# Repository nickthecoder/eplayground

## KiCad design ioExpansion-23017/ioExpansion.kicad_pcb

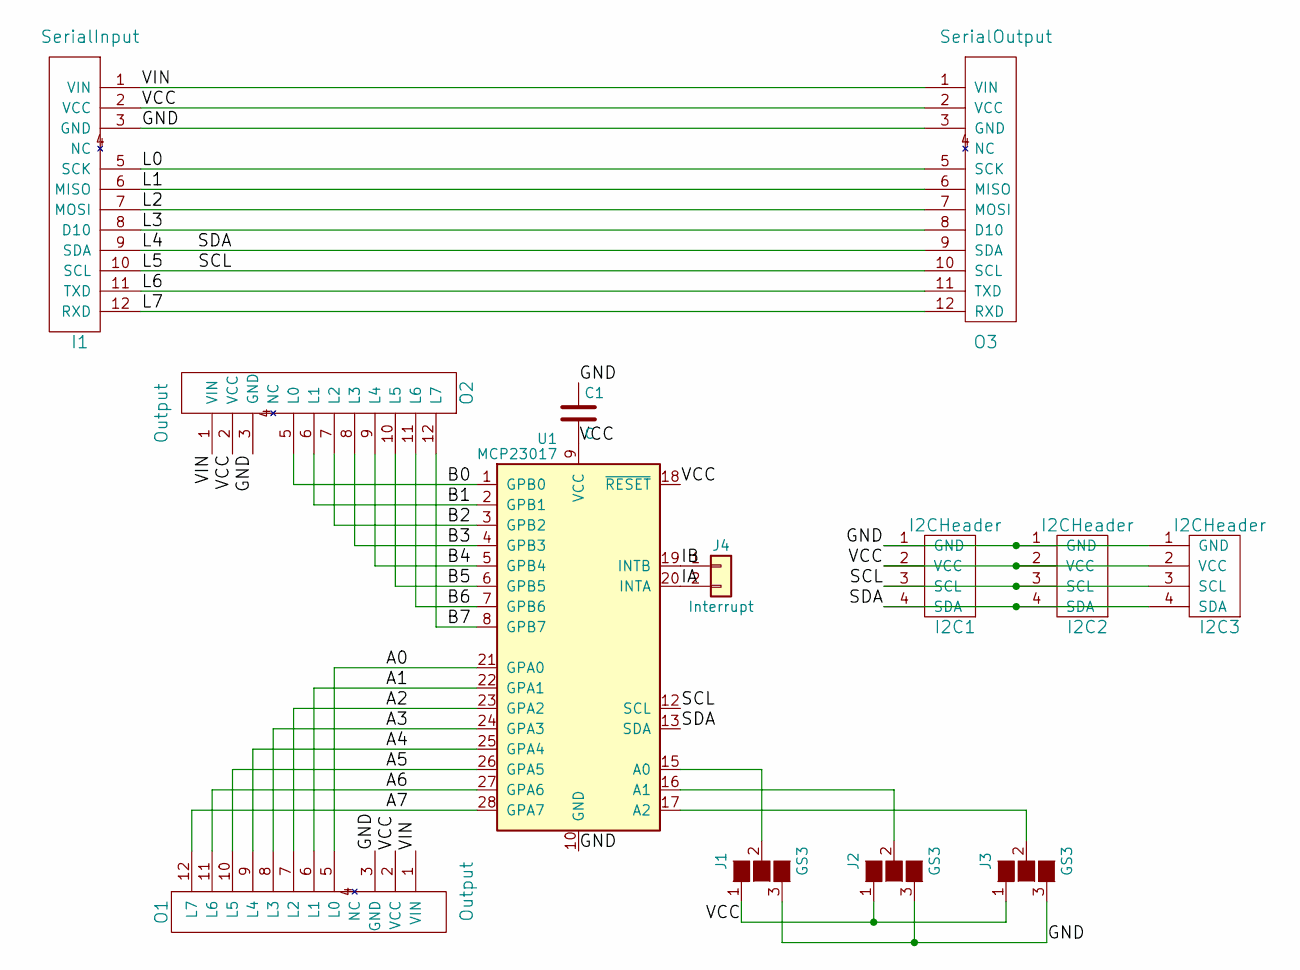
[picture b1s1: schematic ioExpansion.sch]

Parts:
C1: C; C_Disc_D3.8mm_W2.6mm_P2.50mm
I1: SerialInput; Socket_Strip_Straight_1x12_Pitch2.54mm
I2C1, I2C2, I2C3: I2CHeader; Pin_Header_Straight_1x04_Pitch2.54mm
J1, J2, J3: GS3
J4: Interrupt; Pin_Header_Straight_1x02_Pitch2.54mm
O1, O2: Output; Socket_Strip_Straight_1x12_Pitch2.54mm
O3: SerialOutput; Socket_Strip_Straight_1x12_Pitch2.54mm
U1: MCP23017; DIP-28_W7.62mm

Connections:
/A0: O1.5 (L0), U1.21 (GPA0)
/A1: O1.6 (L1), U1.22 (GPA1)
/A2: O1.7 (L2), U1.23 (GPA2)
/A3: O1.8 (L3), U1.24 (GPA3)
/A4: O1.9 (L4), U1.25 (GPA4)
/A5: O1.10 (L5), U1.26 (GPA5)
/A6: O1.11 (L6), U1.27 (GPA6)
/A7: O1.12 (L7), U1.28 (GPA7)
/B0: O2.5 (L0), U1.1 (GPB0)
/B1: O2.6 (L1), U1.2 (GPB1)
/B2: O2.7 (L2), U1.3 (GPB2)
/B3: O2.8 (L3), U1.4 (GPB3)
/B4: O2.9 (L4), U1.5 (GPB4)
/B5: O2.10 (L5), U1.6 (GPB5)
/B6: O2.11 (L6), U1.7 (GPB6)
/B7: O2.12 (L7), U1.8 (GPB7)
/GND: C1.1, I1.3 (GND), I2C1.1 (GND), I2C2.1 (GND), I2C3.1 (GND), J1.3 (G3), J2.3 (G3), J3.3 (G3), O1.3 (GND), O2.3 (GND), O3.3 (GND), U1.10 (GND)
/IA: J4.2, U1.20 (INTA)
/IB: J4.1, U1.19 (INTB)
/L0: I1.5 (SCK), O3.5 (SCK); also elsewhere on the board
/L1: I1.6 (MISO), O3.6 (MISO); also elsewhere on the board
/L2: I1.7 (MOSI), O3.7 (MOSI); also elsewhere on the board
/L3: I1.8 (D10), O3.8 (D10); also elsewhere on the board
/L4: I1.9 (SDA), I2C1.4 (SDA), I2C2.4 (SDA), I2C3.4 (SDA), O3.9 (SDA), U1.13 (SDA); also elsewhere on the board
/L5: I1.10 (SCL), I2C1.3 (SCL), I2C2.3 (SCL), I2C3.3 (SCL), O3.10 (SCL), U1.12 (SCL); also elsewhere on the board
/L6: I1.11 (TXD), O3.11 (TXD); also elsewhere on the board
/L7: I1.12 (RXD), O3.12 (RXD); also elsewhere on the board
/VCC: C1.2, I1.2 (VCC), I2C1.2 (VCC), I2C2.2 (VCC), I2C3.2 (VCC), J1.1 (G1), J2.1 (G1), J3.1 (G1), O1.2 (VCC), O2.2 (VCC), O3.2 (VCC), U1.9 (VCC), U1.18 (~RESET)
/VIN: I1.1 (VIN), O1.1 (VIN), O2.1 (VIN), O3.1 (VIN)
unnamed: J1.2 (G2), U1.15 (A0)
unnamed: J2.2 (G2), U1.16 (A1)
unnamed: J3.2 (G2), U1.17 (A2)

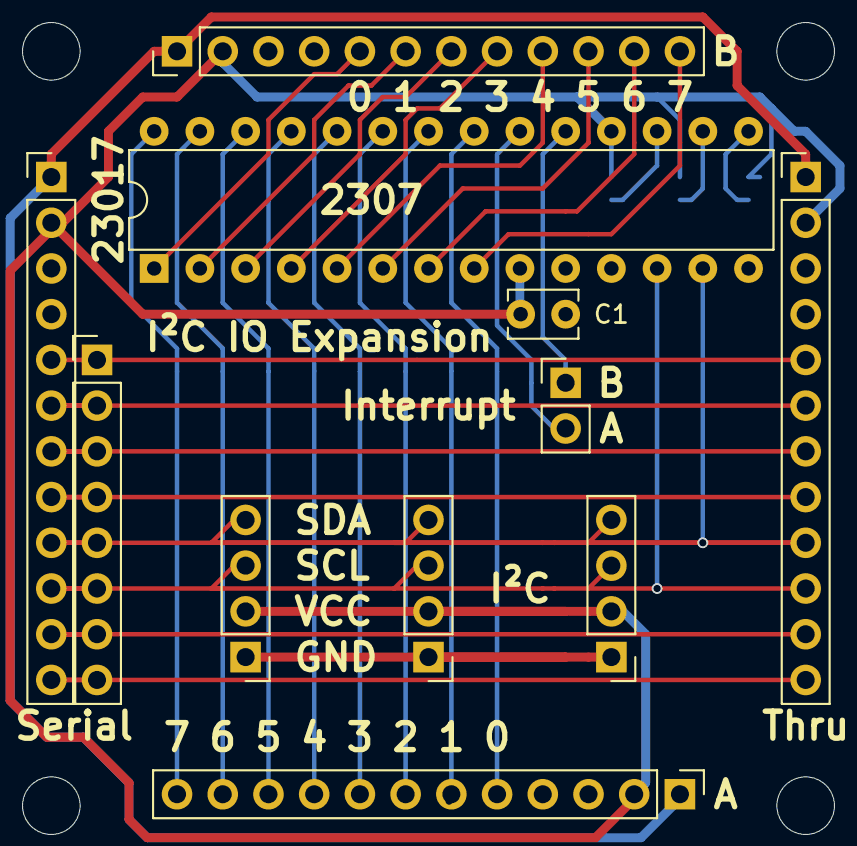
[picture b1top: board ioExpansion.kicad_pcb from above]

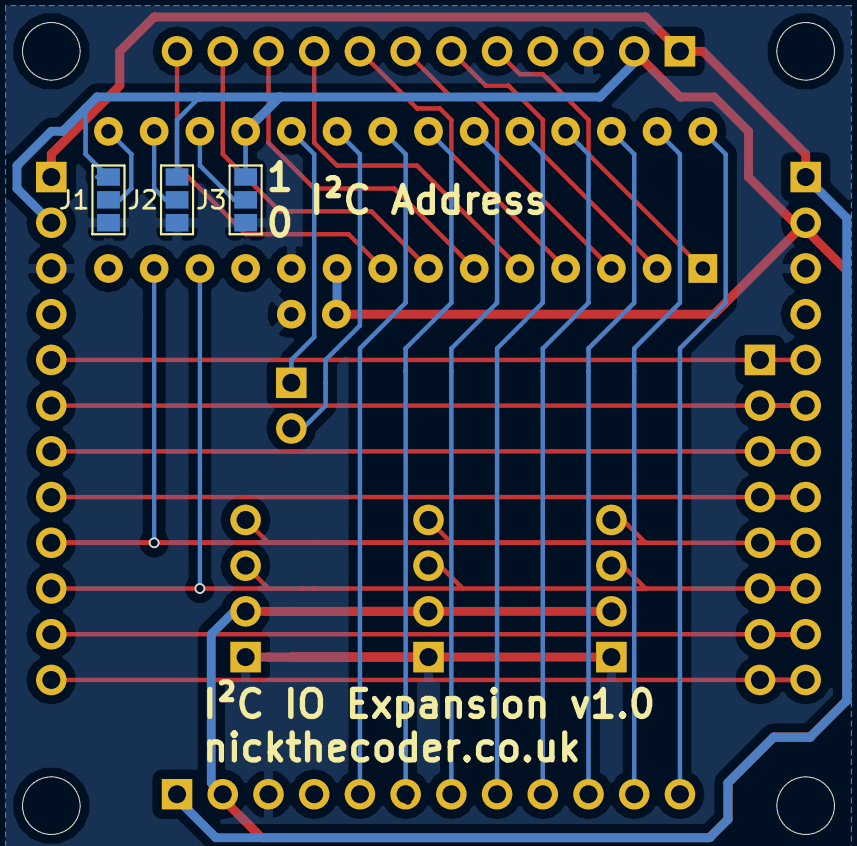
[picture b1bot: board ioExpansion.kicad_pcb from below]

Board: 2 copper layers, 16 parts (3 on the bottom side), 32 nets.

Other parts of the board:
H1: Headers8; Pin_Header_Straight_1x08_Pitch2.54mm
M3, M3#2: MountingHole_3.2mm_M3

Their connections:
/L0: H1.1; also elsewhere on the board
/L1: H1.2; also elsewhere on the board
/L2: H1.3; also elsewhere on the board
/L3: H1.4; also elsewhere on the board
/L4: H1.5; also elsewhere on the board
/L5: H1.6; also elsewhere on the board
/L6: H1.7; also elsewhere on the board
/L7: H1.8; also elsewhere on the board

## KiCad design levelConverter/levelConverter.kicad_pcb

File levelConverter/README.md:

Level Converter
===============

A bi-directional level converter. Place this between a 5V microcontroller, and 3.3V modules.
Uses a voltage regulator to convert the 5V from the microcontroller to 3.3, and mosfets to convert
all eight signals.

## Notes

I think I should have added headers to enable/disable each of the eight lines as it is likely that a project
will need to only convert SOME of the GPIOs. On second thoughts, it should be fine. Need to check!

There is a half-sized version of this module, which uses 9 pin resistor packs, instead of the axial resistors
on this module.

## Version History

### Version 1.0

At the time of writing, I haven't printed (or tested) this module, because I favour the half-sized version.

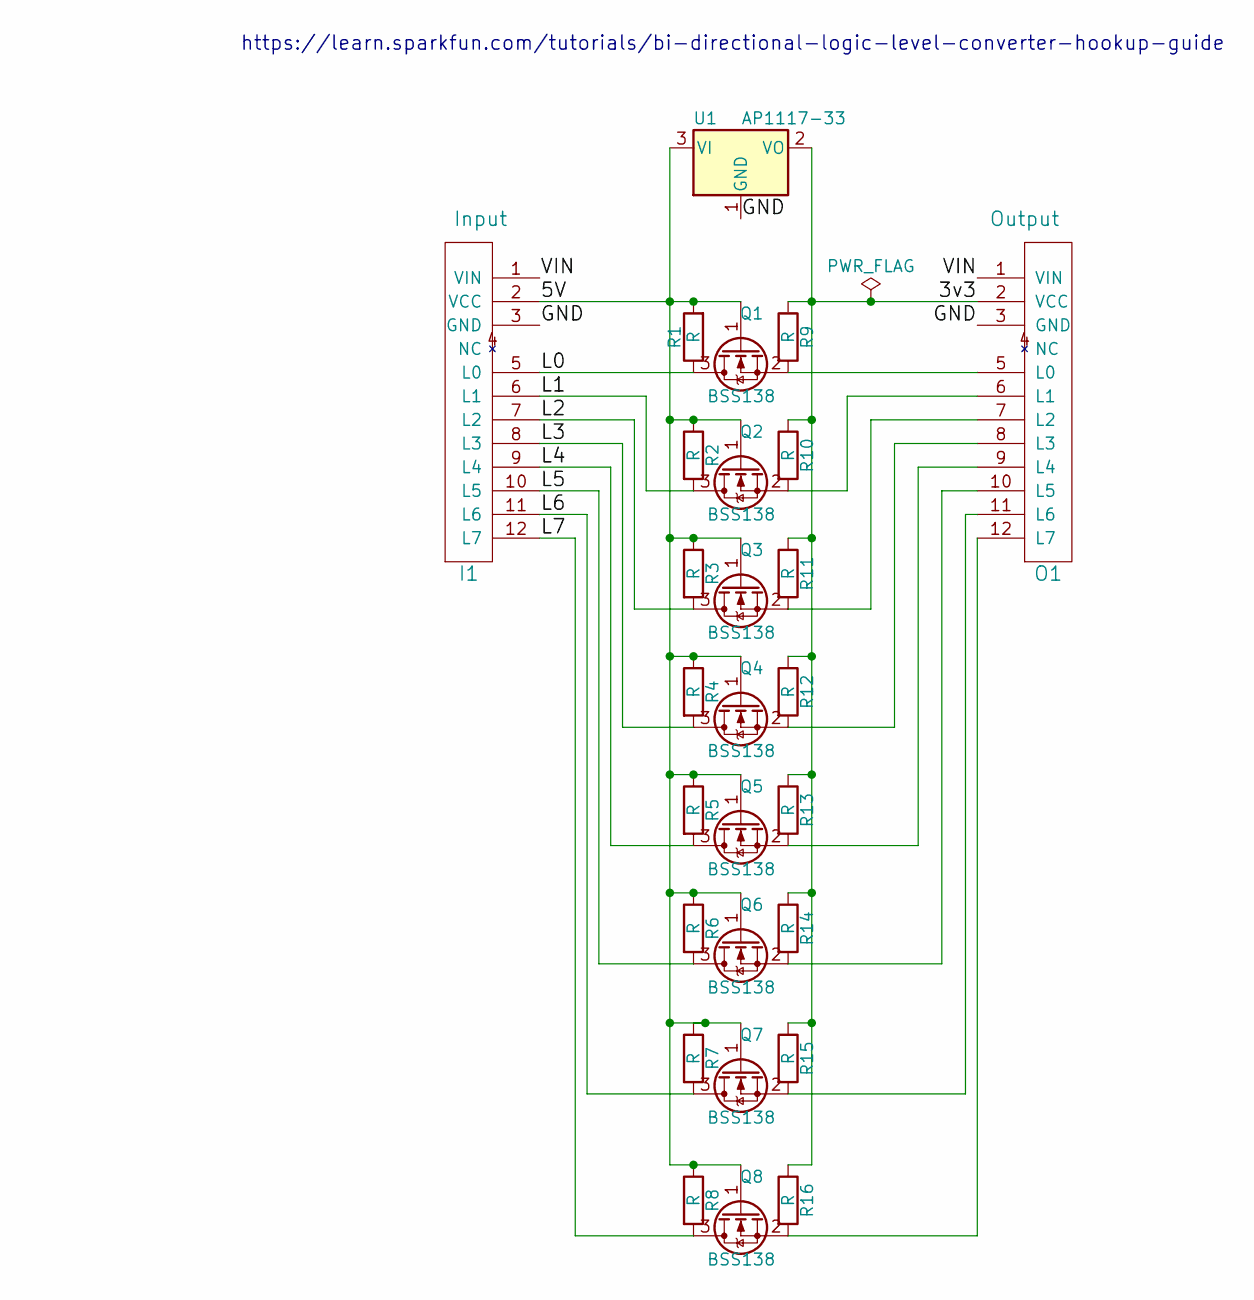
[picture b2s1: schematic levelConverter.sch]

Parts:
I1: Input; Pin_Header_Straight_1x12_Pitch2.54mm
O1: Output; Socket_Strip_Straight_1x12_Pitch2.54mm
Q1, Q2, Q3, Q4, Q5, Q6, Q7, Q8: BSS138; SOT-23
R1, R2, R3, R4, R5, R6, R7, R8, R9, R10, R11, R12, R13, R14, R15, R16: R; R_Axial_DIN0204_L3.6mm_D1.6mm_P7.62mm_Horizontal
U1: AP1117-33; SOT-223-3Lead_TabPin2

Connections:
/3v3: O1.2 (VCC), R9.1, R10.1, R11.1, R12.1, R13.1, R14.1, R15.1, R16.1, U1.2 (VO)
/5V: I1.2 (VCC), Q1.1 (G), Q2.1 (G), Q3.1 (G), Q4.1 (G), Q5.1 (G), Q6.1 (G), Q7.1 (G), Q8.1 (G), R1.2, R2.1, R3.1, R4.1, R5.1, R6.1, R7.1, R8.1, U1.3 (VI)
/GND: I1.3 (GND), O1.3 (GND), U1.1 (GND)
/L0: I1.5 (L0), Q1.3 (D), R1.1
/L1: I1.6 (L1), Q2.3 (D), R2.2
/L2: I1.7 (L2), Q3.3 (D), R3.2
/L3: I1.8 (L3), Q4.3 (D), R4.2
/L4: I1.9 (L4), Q5.3 (D), R5.2
/L5: I1.10 (L5), Q6.3 (D), R6.2
/L6: I1.11 (L6), Q7.3 (D), R7.2
/L7: I1.12 (L7), Q8.3 (D), R8.2
/VIN: I1.1 (VIN), O1.1 (VIN)
unnamed: O1.5 (L0), Q1.2 (S), R9.2
unnamed: O1.6 (L1), Q2.2 (S), R10.2
unnamed: O1.7 (L2), Q3.2 (S), R11.2
unnamed: O1.8 (L3), Q4.2 (S), R12.2
unnamed: O1.9 (L4), Q5.2 (S), R13.2
unnamed: O1.10 (L5), Q6.2 (S), R14.2
unnamed: O1.11 (L6), Q7.2 (S), R15.2
unnamed: O1.12 (L7), Q8.2 (S), R16.2

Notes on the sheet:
https://learn.sparkfun.com/tutorials/bi-directional-logic-level-converter-hookup-guide

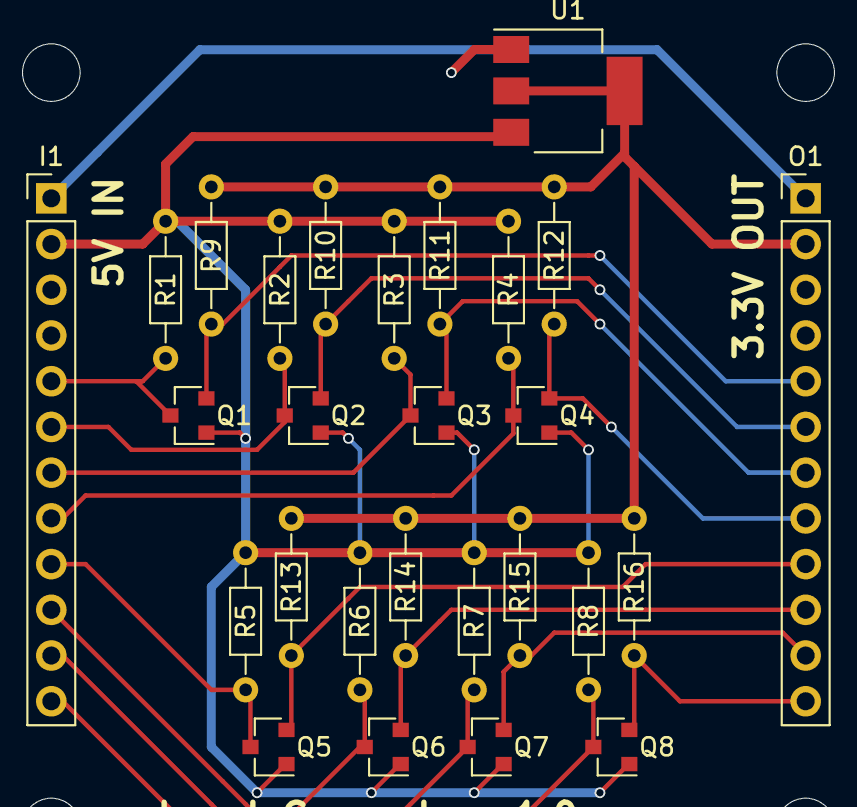
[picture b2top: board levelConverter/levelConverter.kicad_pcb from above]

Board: 2 copper layers, 29 parts (0 on the bottom side), 20 nets.

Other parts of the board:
M3, M3#2: MountingHole_3.2mm_M3

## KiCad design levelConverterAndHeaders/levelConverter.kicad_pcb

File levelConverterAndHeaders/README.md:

Level Converter
===============

A bi-directional level converter. Place this between a 5V microcontroller, and 3.3V modules.
Uses a voltage regulator to convert the 5V from the microcontroller to 3.3, and mosfets to convert
all eight signals.

This is a half-sized module. There is also a full sized module, which uses regular axial resistors, instead of the
9 pin resistor networks used by this module. The choice is yours!

Headers
=======

Another half-sized module, which exposes each data pin in a triple header, with VCC and GND.
This is particularly useful for servos.

## Version History

### Version 1.0

At the time of writing I haven't tested these modules.

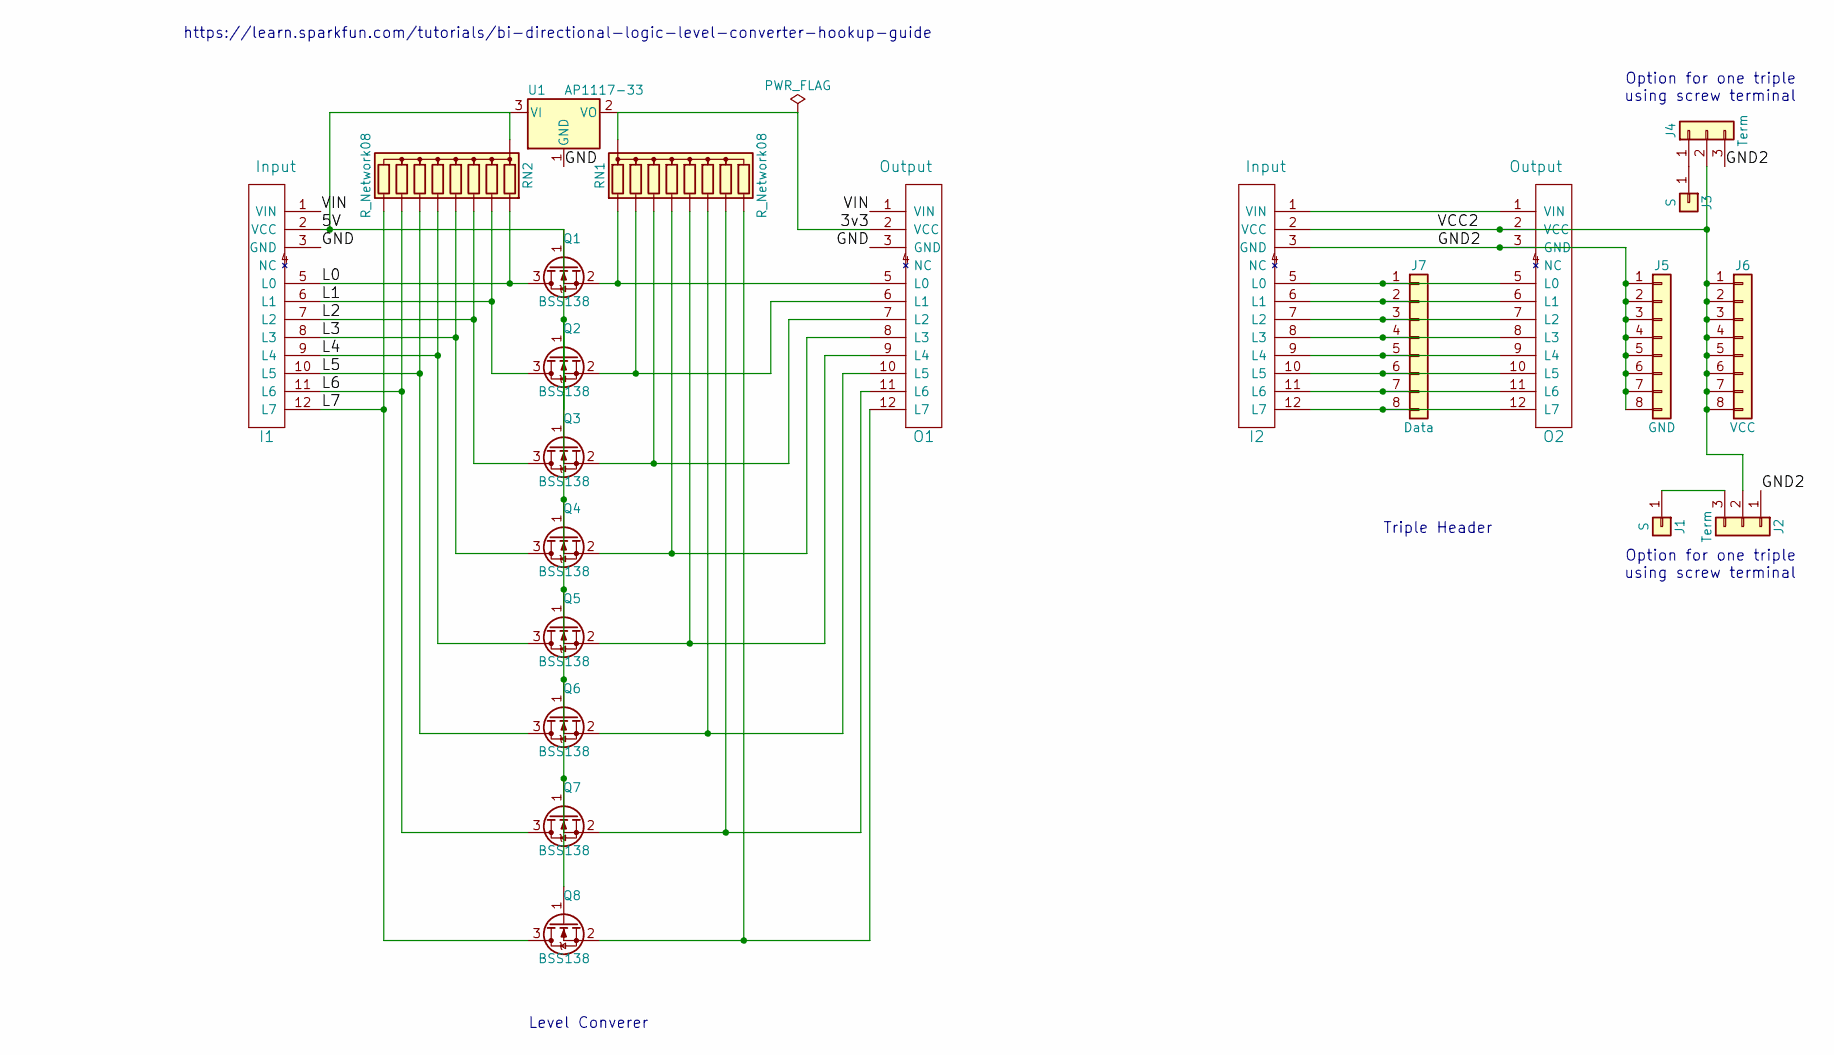
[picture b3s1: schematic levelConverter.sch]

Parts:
I1, I2: Input; Pin_Header_Straight_1x12_Pitch2.54mm
J1, J3: S; Pin_Header_Straight_1x01_Pitch2.54mm
J2, J4: Term; TerminalBlock_Pheonix_MPT-2.54mm_3pol
J5: GND; Pin_Header_Straight_1x08_Pitch2.54mm
J6: VCC; Pin_Header_Straight_1x08_Pitch2.54mm
J7: Data; Pin_Header_Straight_1x08_Pitch2.54mm
O1, O2: Output; Socket_Strip_Straight_1x12_Pitch2.54mm
Q1, Q2, Q3, Q4, Q5, Q6, Q7, Q8: BSS138; SOT-23
RN1, RN2: R_Network08; R_Array_SIP9
U1: AP1117-33; SOT-223-3Lead_TabPin2

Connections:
/3v3: O1.2 (VCC), RN1.1 (common), U1.2 (VO)
/5V: I1.2 (VCC), Q1.1 (G), Q2.1 (G), Q3.1 (G), Q4.1 (G), Q5.1 (G), Q6.1 (G), Q7.1 (G), Q8.1 (G), RN2.1 (common), U1.3 (VI)
/GND: I1.3 (GND), O1.3 (GND), U1.1 (GND)
/GND2: I2.3 (GND), J2.1, J4.3, J5.1, J5.2, J5.3, J5.4, J5.5, J5.6, J5.7, J5.8, O2.3 (GND)
/L0: I1.5 (L0), Q1.3 (D), RN2.2 (R1)
/L1: I1.6 (L1), Q2.3 (D), RN2.3 (R2)
/L2: I1.7 (L2), Q3.3 (D), RN2.4 (R3)
/L3: I1.8 (L3), Q4.3 (D), RN2.5 (R4)
/L4: I1.9 (L4), Q5.3 (D), RN2.6 (R5)
/L5: I1.10 (L5), Q6.3 (D), RN2.7 (R6)
/L6: I1.11 (L6), Q7.3 (D), RN2.8 (R7)
/L7: I1.12 (L7), Q8.3 (D), RN2.9 (R8)
/VCC2: I2.2 (VCC), J2.2, J4.2, J6.1, J6.2, J6.3, J6.4, J6.5, J6.6, J6.7, J6.8, O2.2 (VCC)
/VIN: I1.1 (VIN), O1.1 (VIN)
unnamed: I2.1 (VIN), O2.1 (VIN)
unnamed: I2.5 (L0), J7.1, O2.5 (L0)
unnamed: I2.6 (L1), J7.2, O2.6 (L1)
unnamed: I2.7 (L2), J7.3, O2.7 (L2)
unnamed: I2.8 (L3), J7.4, O2.8 (L3)
unnamed: I2.9 (L4), J7.5, O2.9 (L4)
unnamed: I2.10 (L5), J7.6, O2.10 (L5)
unnamed: I2.11 (L6), J7.7, O2.11 (L6)
unnamed: I2.12 (L7), J7.8, O2.12 (L7)
unnamed: J1.1, J2.3
unnamed: J3.1, J4.1
unnamed: O1.5 (L0), Q1.2 (S), RN1.2 (R1)
unnamed: O1.6 (L1), Q2.2 (S), RN1.3 (R2)
unnamed: O1.7 (L2), Q3.2 (S), RN1.4 (R3)
unnamed: O1.8 (L3), Q4.2 (S), RN1.5 (R4)
unnamed: O1.9 (L4), Q5.2 (S), RN1.6 (R5)
unnamed: O1.10 (L5), Q6.2 (S), RN1.7 (R6)
unnamed: O1.11 (L6), Q7.2 (S), RN1.8 (R7)
unnamed: O1.12 (L7), Q8.2 (S), RN1.9 (R8)

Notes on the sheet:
https://learn.sparkfun.com/tutorials/bi-directional-logic-level-converter-hookup-guide
Level Converer
Triple Header
Option for one triple using screw terminal

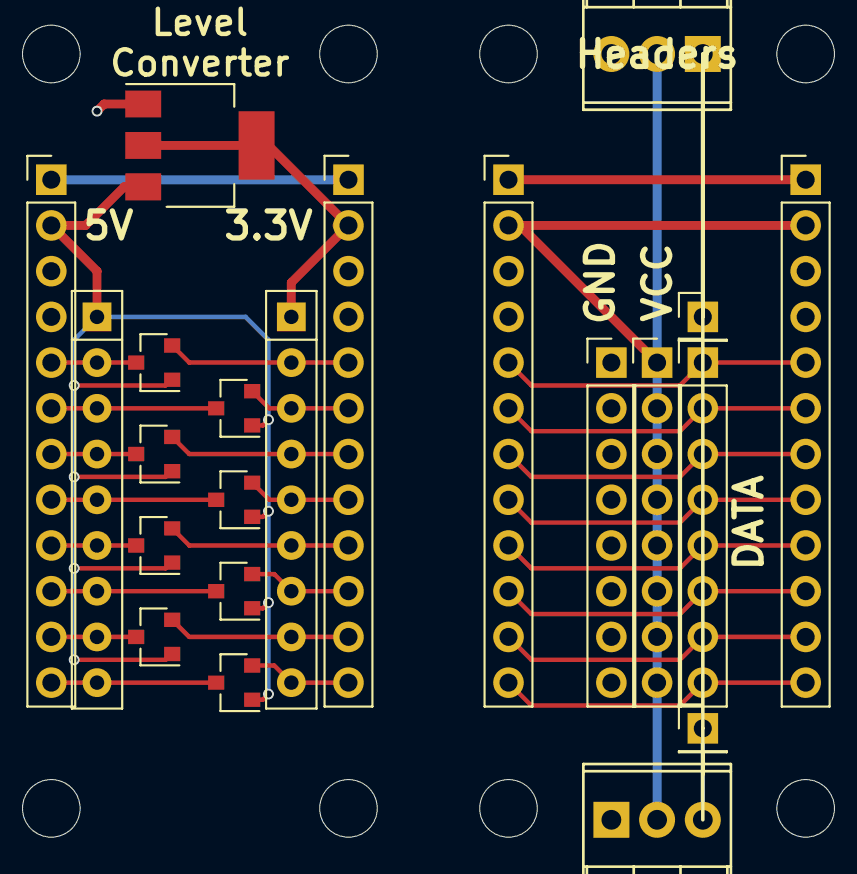
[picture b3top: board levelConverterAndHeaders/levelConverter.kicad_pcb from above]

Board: 2 copper layers, 26 parts (0 on the bottom side), 33 nets.

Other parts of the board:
M3, M3#2, M3#3, M3#4: MountingHole_3.2mm_M3

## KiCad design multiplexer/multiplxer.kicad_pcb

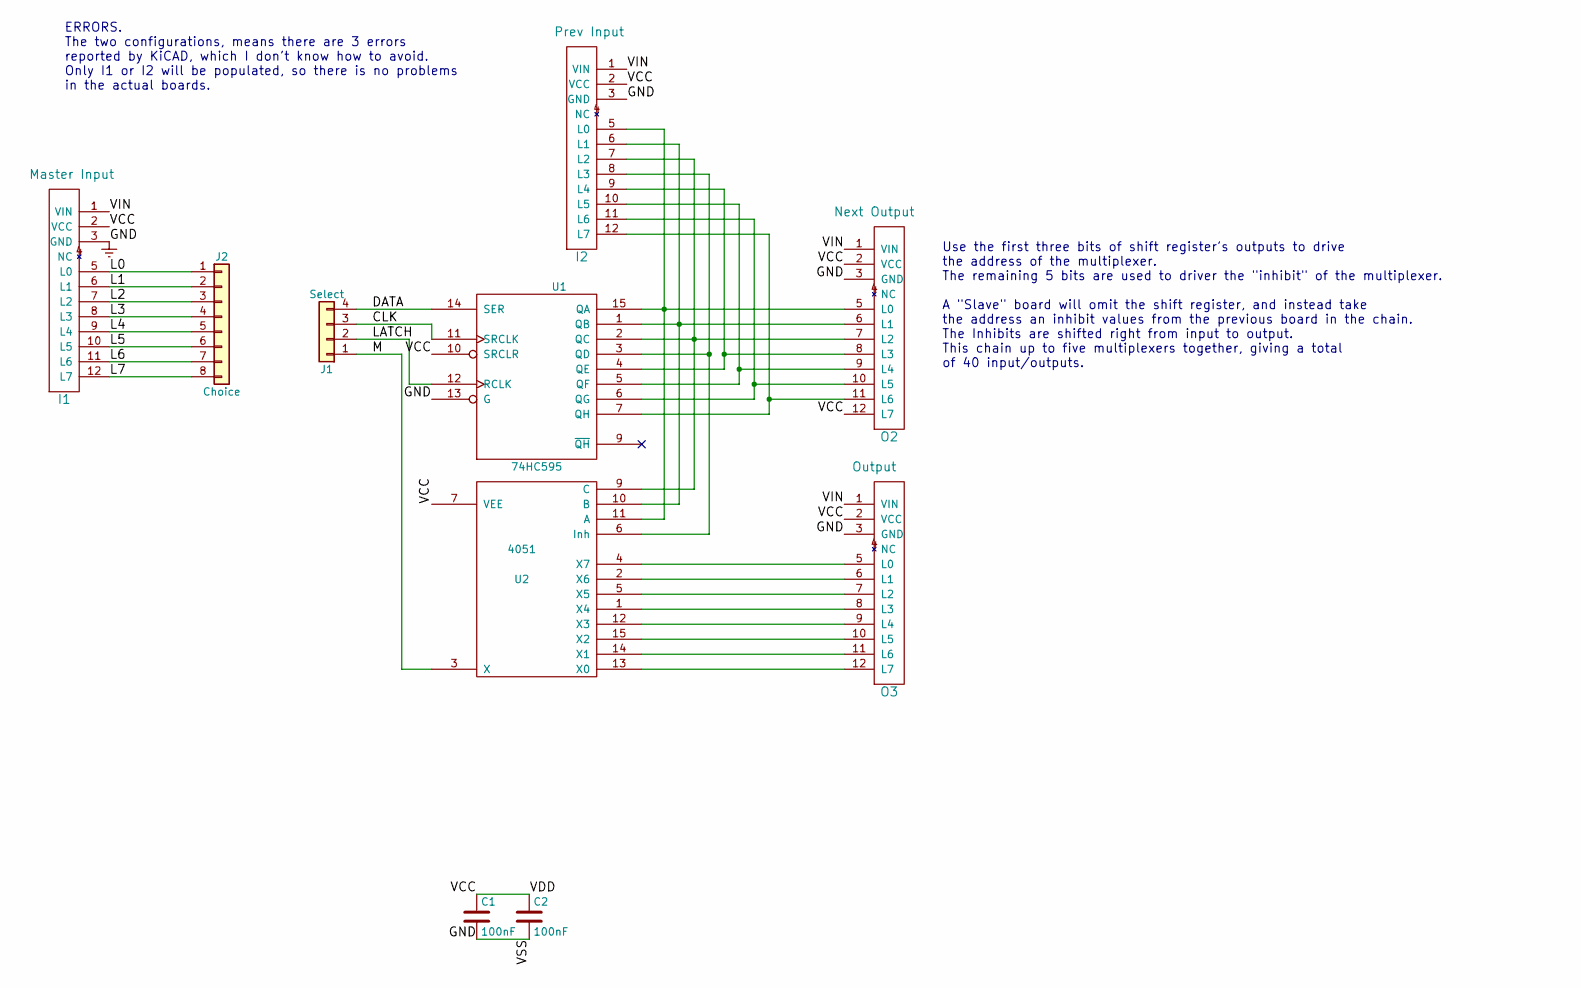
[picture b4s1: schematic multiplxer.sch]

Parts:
C1, C2: 100nF; C_Disc_D3.8mm_W2.6mm_P2.50mm
I1: Master Input; Pin_Header_Straight_1x12_Pitch2.54mm
I2: Prev Input; Pin_Header_Straight_1x12_Pitch2.54mm
J1: Select; Pin_Header_Straight_1x04_Pitch2.54mm
J2: Choice; Pin_Header_Straight_1x08_Pitch2.54mm
O2: Next Output; Socket_Strip_Straight_1x12_Pitch2.54mm
O3: Output; Socket_Strip_Straight_1x12_Pitch2.54mm
U1: 74HC595; DIP-16_W7.62mm
U2: 4051; DIP-16_W7.62mm

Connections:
/CLK: J1.3, U1.11 (SRCLK)
/DATA: J1.4, U1.14 (SER)
/L0: I1.5 (L0), J2.1
/L1: I1.6 (L1), J2.2
/L2: I1.7 (L2), J2.3
/L3: I1.8 (L3), J2.4
/L4: I1.9 (L4), J2.5
/L5: I1.10 (L5), J2.6
/L6: I1.11 (L6), J2.7
/L7: I1.12 (L7), J2.8
/LATCH: J1.2, U1.12 (RCLK)
/M: J1.1, U2.3 (X)
/VIN: I1.1 (VIN), I2.1 (VIN), O2.1 (VIN), O3.1 (VIN)
Earth: C1.2, C2.2, I1.3 (GND), I2.3 (GND), O2.3 (GND), O3.3 (GND), U1.8 (GND), U1.13 (G), U2.8 (VSS)
unnamed: I2.5 (L0), O2.5 (L0), U1.15 (QA), U2.11 (A)
unnamed: I2.6 (L1), O2.6 (L1), U1.1 (QB), U2.10 (B)
unnamed: I2.7 (L2), O2.7 (L2), U1.2 (QC), U2.9 (C)
unnamed: I2.8 (L3), U1.3 (QD), U2.6 (Inh)
unnamed: I2.9 (L4), O2.8 (L3), U1.4 (QE)
unnamed: I2.10 (L5), O2.9 (L4), U1.5 (QF)
unnamed: I2.11 (L6), O2.10 (L5), U1.6 (QG)
unnamed: I2.12 (L7), O2.11 (L6), U1.7 (QH)
unnamed: O3.5 (L0), U2.4 (X7)
unnamed: O3.6 (L1), U2.2 (X6)
unnamed: O3.7 (L2), U2.5 (X5)
unnamed: O3.8 (L3), U2.1 (X4)
unnamed: O3.9 (L4), U2.12 (X3)
unnamed: O3.10 (L5), U2.15 (X2)
unnamed: O3.11 (L6), U2.14 (X1)
unnamed: O3.12 (L7), U2.13 (X0)
VCC: C1.1, C2.1, I1.2 (VCC), I2.2 (VCC), O2.2 (VCC), O2.12 (L7), O3.2 (VCC), U1.10 (SRCLR), U1.16 (VCC), U2.7 (VEE), U2.16 (VDD)

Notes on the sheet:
Use the first three bits of shift register's outputs to drive the address of the multiplexer. The remaining 5 bits are used to driver the "inhibit" of the multiplexer. A "Slave" board will omit the shift register, and instead take the address an inhibit values from the previous board in the chain. 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
ERRORS. The two configurations, means there are 3 errors reported by KiCAD, which I don't know how to avoid. Only I1 or I2 will be populated, so there is no problems in the actual boards.

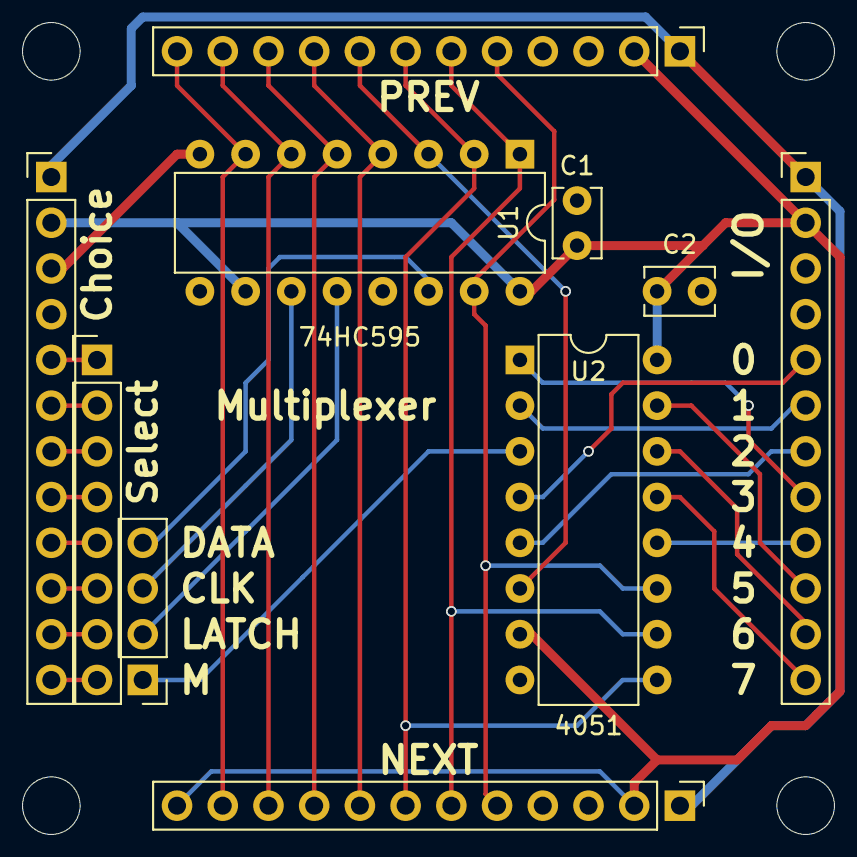
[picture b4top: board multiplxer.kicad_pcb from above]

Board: 2 copper layers, 12 parts (0 on the bottom side), 31 nets.

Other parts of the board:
M3, M3#2: MountingHole_3.2mm_M3

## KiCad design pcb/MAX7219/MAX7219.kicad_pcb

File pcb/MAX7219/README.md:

MAX 7219
========

The MAX 7219 can drive six eight segment displays, or a 6x8 LED matrix, as well as upto 16 buttons.

The module only has 8 buttons, however, you can switch between the two banks of buttons using a switch.

The outputs for the leds are exposed as simple header pins.

## Version History

### Version 1.0

At the time of writing, I haven't tested this module.

The name of the module is missing. It reads "Module Name". Oops.

### Version 1.1

Not printed.

Corrected the module name.

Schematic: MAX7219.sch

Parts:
C1, C2: 100pF; C_Disc_D3.0mm_W1.6mm_P2.50mm
H1: Headers8L; Pin_Header_Straight_1x08_Pitch2.54mm
I1: SerialInput; Pin_Header_Straight_1x12_Pitch2.54mm
J1: Conn_01x02; Pin_Header_Straight_1x02_Pitch2.54mm
J2: Conn_01x08; Pin_Header_Straight_1x08_Pitch2.54mm
J3: Conn_01x06; Pin_Header_Straight_1x06_Pitch2.54mm
O1: Output; Socket_Strip_Straight_1x12_Pitch2.54mm
SW1, SW2, SW3, SW4, SW5, SW6, SW7, SW8: SW_SPST; SW_SPST_EVQP0
SW9: SW_SPDT; SW_CuK_JS202011CQN_DPDT_Straight
U1: TM1637; DIP-20_W7.62mm

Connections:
/CLK: C1.2, J1.1, U1.18 (CLK)
/DIO: C2.1, J1.2, U1.17 (DIO)
/SCL: H1.6 (H6), I1.10 (SCL), O1.10 (L5)
/SDA: H1.5 (H5), I1.9 (SDA), O1.9 (L4)
/VCC: I1.2 (VCC), O1.2 (VCC), U1.16 (VDD)
/VIN: I1.1 (VIN), O1.1 (VIN)
Earth: C1.1, C2.2, I1.3 (GND), O1.3 (GND), U1.1 (GND)
unnamed: H1.1 (H1), I1.5 (SCK), O1.5 (L0)
unnamed: H1.2 (H2), I1.6 (MISO), O1.6 (L1)
unnamed: H1.3 (H3), I1.7 (MOSI), O1.7 (L2)
unnamed: H1.4 (H4), I1.8 (D10), O1.8 (L3)
unnamed: H1.7 (H7), I1.11 (TXD), O1.11 (L6)
unnamed: H1.8 (H8), I1.12 (RXD), O1.12 (L7)
unnamed: J2.1, SW1.1 (A), U1.2 (SEG1)
unnamed: J2.2, SW2.1 (A), U1.3 (SEG2)
unnamed: J2.3, SW3.1 (A), U1.4 (SEG3)
unnamed: J2.4, SW4.1 (A), U1.5 (SEG4)
unnamed: J2.5, SW5.1 (A), U1.6 (SEG5)
unnamed: J2.6, SW6.1 (A), U1.7 (SEG6)
unnamed: J2.7, SW7.1 (A), U1.8 (SEG7)
unnamed: J2.8, SW8.1 (A), U1.9 (SEG8)
unnamed: J3.1, U1.15 (GRID1)
unnamed: J3.2, U1.14 (GRID2)
unnamed: J3.3, U1.13 (GRID3)
unnamed: J3.4, U1.12 (GRID4)
unnamed: J3.5, U1.11 (GRID5)
unnamed: J3.6, U1.10 (GRID6)
unnamed: SW1.2 (B), SW2.2 (B), SW3.2 (B), SW4.2 (B), SW5.2 (B), SW6.2 (B), SW7.2 (B), SW8.2 (B), SW9.2
unnamed: SW9.1, U1.19 (K1)
unnamed: SW9.3, U1.20 (K2)

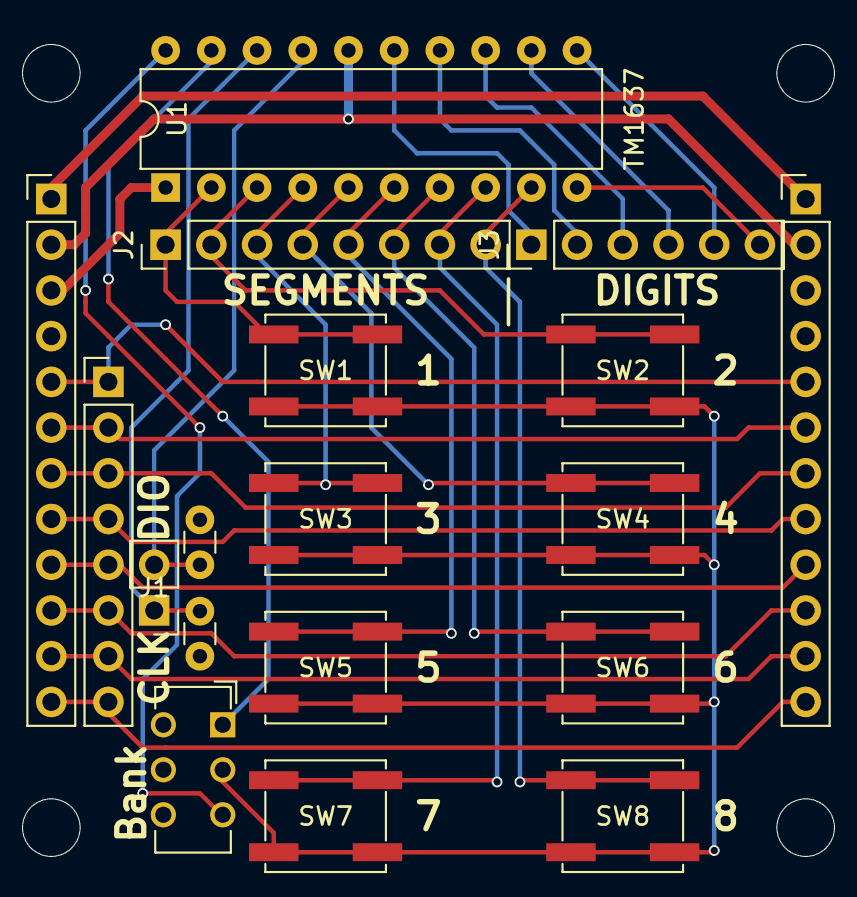
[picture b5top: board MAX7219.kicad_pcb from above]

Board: 2 copper layers, 20 parts (0 on the bottom side), 30 nets.

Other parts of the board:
M3, M3#2: MountingHole_3.2mm_M3

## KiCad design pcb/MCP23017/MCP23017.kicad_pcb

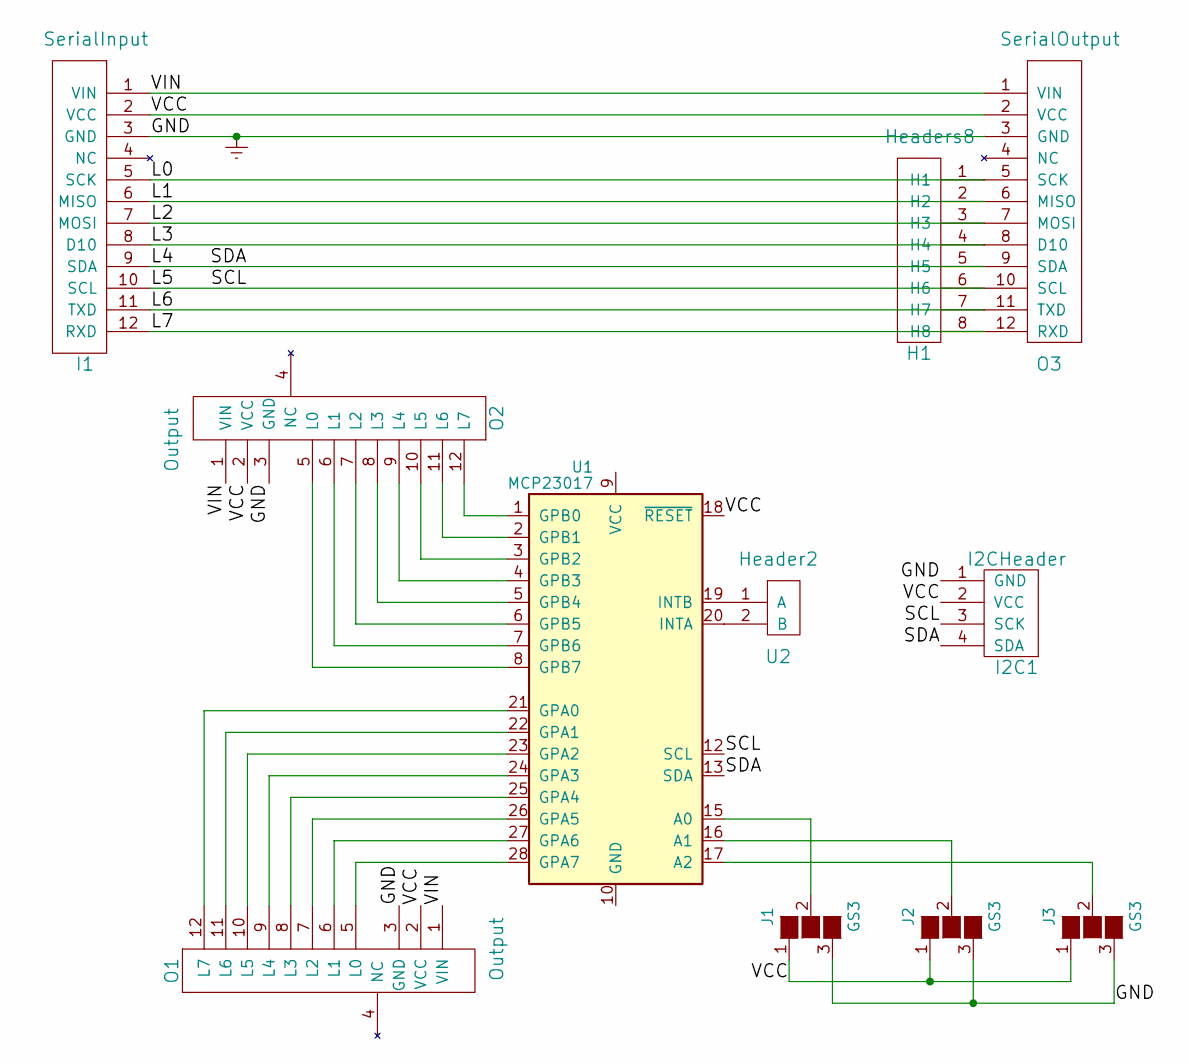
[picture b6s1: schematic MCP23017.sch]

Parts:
H1: Headers8; Pin_Header_Straight_1x08_Pitch2.54mm
I1: SerialInput; Socket_Strip_Straight_1x12_Pitch2.54mm
I2C1: I2CHeader; Pin_Header_Straight_1x04_Pitch2.54mm
J1, J2, J3: GS3
O1, O2: Output; Socket_Strip_Straight_1x12_Pitch2.54mm
O3: SerialOutput; Socket_Strip_Straight_1x12_Pitch2.54mm
U1: MCP23017; DIP-28_W7.62mm
U2: Header2; Pin_Header_Straight_1x02_Pitch2.54mm

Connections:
/L0: H1.1 (H1), I1.5 (SCK), O3.5 (SCK)
/L1: H1.2 (H2), I1.6 (MISO), O3.6 (MISO)
/L2: H1.3 (H3), I1.7 (MOSI), O3.7 (MOSI)
/L3: H1.4 (H4), I1.8 (D10), O3.8 (D10)
/L4: H1.5 (H5), I1.9 (SDA), I2C1.4 (SDA), O3.9 (SDA), U1.13 (SDA)
/L5: H1.6 (H6), I1.10 (SCL), I2C1.3 (SCK), O3.10 (SCL), U1.12 (SCL)
/L6: H1.7 (H7), I1.11 (TXD), O3.11 (TXD)
/L7: H1.8 (H8), I1.12 (RXD), O3.12 (RXD)
/VCC: I1.2 (VCC), I2C1.2 (VCC), J1.1 (G1), J2.1 (G1), J3.1 (G1), O1.2 (VCC), O2.2 (VCC), O3.2 (VCC), U1.18 (~RESET)
/VIN: I1.1 (VIN), O1.1 (VIN), O2.1 (VIN), O3.1 (VIN)
Earth: I1.3 (GND), I2C1.1 (GND), J1.3 (G3), J2.3 (G3), J3.3 (G3), O1.3 (GND), O2.3 (GND), O3.3 (GND)
unnamed: J1.2 (G2), U1.15 (A0)
unnamed: J2.2 (G2), U1.16 (A1)
unnamed: J3.2 (G2), U1.17 (A2)
unnamed: O1.5 (L0), U1.28 (GPA7)
unnamed: O1.6 (L1), U1.27 (GPA6)
unnamed: O1.7 (L2), U1.26 (GPA5)
unnamed: O1.8 (L3), U1.25 (GPA4)
unnamed: O1.9 (L4), U1.24 (GPA3)
unnamed: O1.10 (L5), U1.23 (GPA2)
unnamed: O1.11 (L6), U1.22 (GPA1)
unnamed: O1.12 (L7), U1.21 (GPA0)
unnamed: O2.5 (L0), U1.8 (GPB7)
unnamed: O2.6 (L1), U1.7 (GPB6)
unnamed: O2.7 (L2), U1.6 (GPB5)
unnamed: O2.8 (L3), U1.5 (GPB4)
unnamed: O2.9 (L4), U1.4 (GPB3)
unnamed: O2.10 (L5), U1.3 (GPB2)
unnamed: O2.11 (L6), U1.2 (GPB1)
unnamed: O2.12 (L7), U1.1 (GPB0)
unnamed: U1.19 (INTB), U2.1 (A)
unnamed: U1.20 (INTA), U2.2 (B)

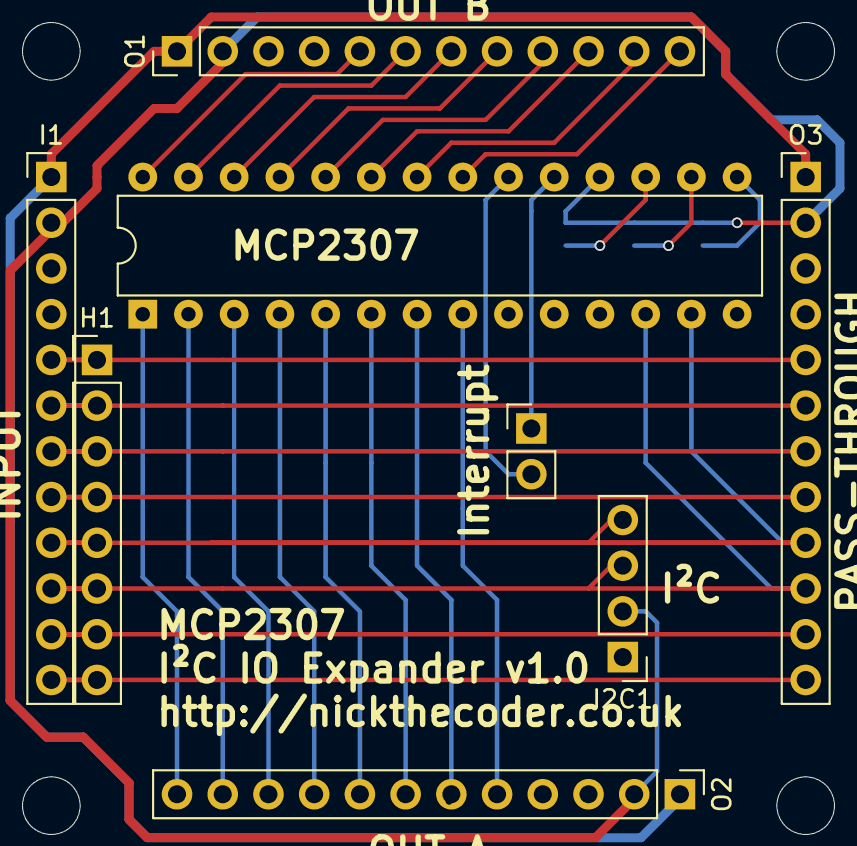
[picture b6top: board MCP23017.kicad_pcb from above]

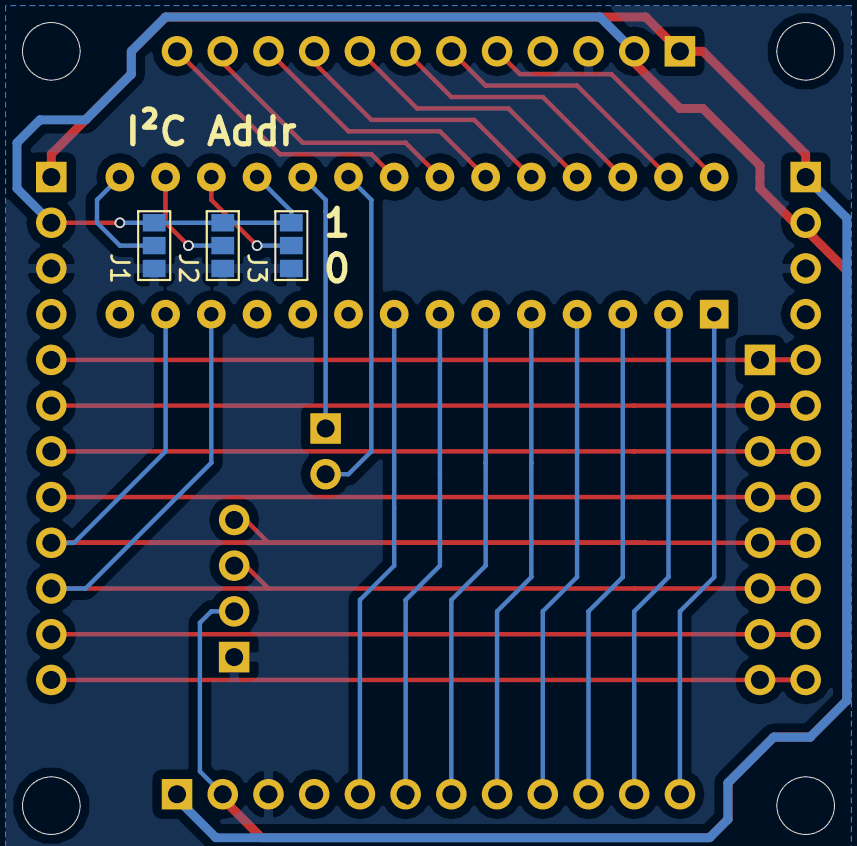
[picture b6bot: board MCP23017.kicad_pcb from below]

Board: 2 copper layers, 13 parts (3 on the bottom side), 32 nets.

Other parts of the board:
M3, M3#2: MountingHole_3.2mm_M3
